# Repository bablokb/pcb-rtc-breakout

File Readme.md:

PCB-RTC-Breakout
================

This is a minimalistic pcb to add a normal DS3131-breakout to a
Raspberry Pi:

Note that you have to remove the 32K-pin of the breakout and that
you might have to bend the other pins.

The pcb also adds a connector for a button. With the correct
configuration of the Pi you can now start and stop the Pi cleanly
with the button and start it in addition with the alarm of the RTC.

Note that the normal I2C-bus in not available when the button is
populated and configured.

Schematic
---------

The pcb just connects the I2C-lines of the RTC-breakout to GPIO17 and
GPIO27. Normal I2C is not available, since GPIO3 is needed for the
shutdown/restart function.

PCB-production
--------------

The pcb-definition (Kicad-format) is in the directory `rtc-breakout.kicad`.
If your favorite pcb-factory does not support Kicad directly, you can
export to Gerber from within Kicad.

Configuration
-------------

In `/boot/config.txt`, add the following lines:

    dtoverlay=i2c-rtc-gpio,ds3231,i2c_gpio_sda=17,i2c_gpio_scl=27,wakeup-source
    dtoverlay=gpio-shutdown

The first line configures the RTC, the second line configures the button
to initiate a shutdown. If you do not cut power, a second press of the
button will restart the Pi.

License
-------

Shield: [![CC BY-SA 4.0][cc-by-sa-shield]][cc-by-sa]

This work is licensed under a
[Creative Commons Attribution-ShareAlike 4.0 International
License][cc-by-sa].

[![CC BY-SA 4.0][cc-by-sa-image]][cc-by-sa]

[cc-by-sa]: http://creativecommons.org/licenses/by-sa/4.0/
[cc-by-sa-image]: https://licensebuttons.net/l/by-sa/4.0/88x31.png
[cc-by-sa-shield]:
https://img.shields.io/badge/License-CC%20BY--SA%204.0-lightgrey.svg

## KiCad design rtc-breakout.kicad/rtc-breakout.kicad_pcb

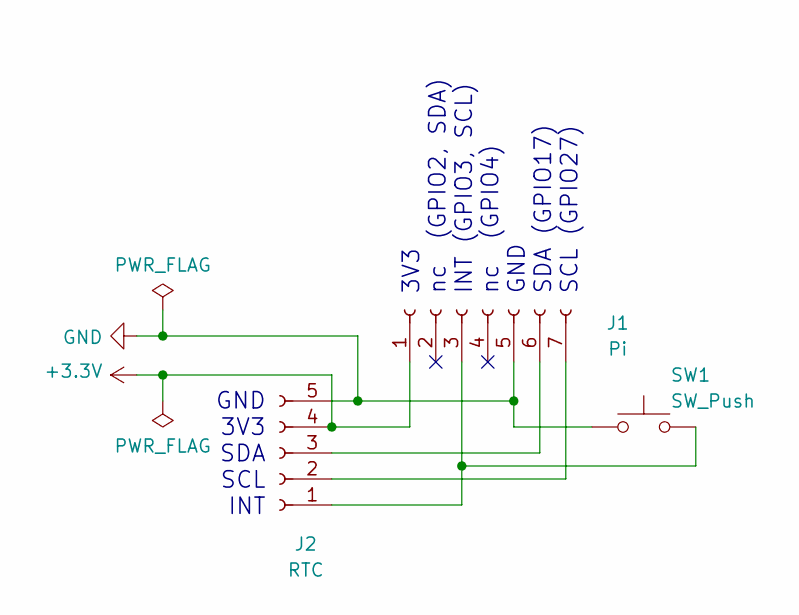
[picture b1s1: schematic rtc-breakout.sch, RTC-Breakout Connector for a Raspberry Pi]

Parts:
J1: Pi; PinSocket_1x07_P2.54mm_Vertical
J2: RTC; PinSocket_1x05_P2.54mm_Vertical
SW1: SW_Push; SW_PUSH_6mm

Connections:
+3V3: J1.1, J2.4
GND: J1.5, J2.5, SW1.1
unnamed: J1.3, J2.1, SW1.2
unnamed: J1.6, J2.3
unnamed: J1.7, J2.2

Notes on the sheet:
GND 3V3 SDA SCL INT
3V3 nc (GPIO2, SDA) INT (GPIO3, SCL) nc (GPIO4) GND SDA (GPIO17) SCL (GPIO27)

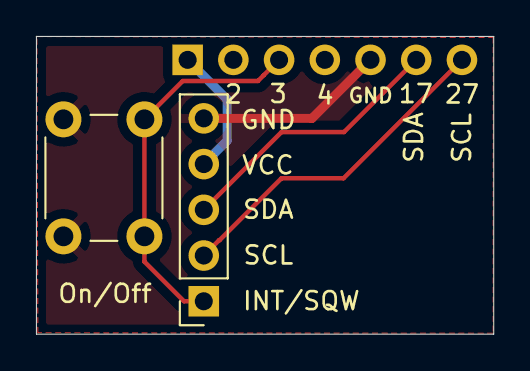
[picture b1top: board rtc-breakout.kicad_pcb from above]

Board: 2 copper layers, 25.4 x 16.5 mm, 3 parts (1 on the bottom side), 5 nets.

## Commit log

2020-06-25 updated labels
2021-10-30 changed LICENSE to CC-BY-SA
2021-10-30 added section about license
